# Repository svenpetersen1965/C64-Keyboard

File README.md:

# Status
Realeased: 2026-10-11  
# C64-Keyboard
A mechanical keyboard for the C64.
*	<b>Reset</b>: The keyboard can generate RESET and EXROM RESET signals.
*	<b>Kernal switching</b>: The keyboard can switch between multiple Kernals on an EPROM Kernal adapter.
*	<b>OLED display</b>: An I²C OLED display can be connected to the keyboard.
*	<b>Piezo buzzer</b>: The keyboard includes a piezo buzzer for signaling.
*	<b>USB keyboard</b>: The keyboard can be operated as a USB keyboard for VICE and BMC64.
*	<b>RGB lighting</b>: The keyboard can produce a light show using a WS2812B RGB LED strip.
*	<b>Power LED</b>: The C64's power LED can be connected to the keyboard on either the left or right side and can be made to blink.
*	<b>Additional buttons</b>: Two additional buttons beside the shorter space bar provide additional control functions.
*   <b>Ultimate 64 elite II buttons</b>: Control MENU/FREEZE/RESET with the keyboard. No extra buttons need to be installed

After about 21 months of work, the day has finally come: I’m releasing my Commodore C64 keyboard project on GitHub!

I haven’t been working on it full-time, of course, but I’ve still put several person-months of work into it (most of it for documentation). And I’ve certainly spent a few thousand euros along the way (so you don't have to).

<p align="center">The C64 mechanic Keyboard and the USB-Keyboard version for VICE and BMC64</p>

My goal was to build a complete keyboard, including the keycaps, and figure out a way for others with some DIY skills to build one, too, without having to spend anywhere near as much money.

Let me be clear, though: this isn’t meant to be a cheap replacement for an original C64 keyboard. It’s for people who use a C64, an Ultimate 64, or another C64-compatible system and enjoy mechanical keyboards. If you’d like to build your own keyboard and add some extra functionality to your setup, this project might be just what you’re looking for.

The documentation is around 80 pages long, but most of it consists of pictures, and you don't need to read every single page. I'd really appreciate it, though, if you took the time to understand the important parts. Otherwise, I might end up providing support for years to come, and I'd rather spend that time working on new projects!

The bill of materials (BOM) is quite flexible. You don't need all the components; you can populate only the parts required for your intended setup. I've designed the BOM to make this as straightforward as possible.

However, you should decide which features you need before ordering the components. Even if you fully populate the board, none of the unused circuits will interfere with the keyboard's normal operation.

I'd like to draw your attention to the following important sections of the documentation:
*	<b>Hardware description</b>: <a href="https://github.com/svenpetersen1965/C64-Keyboard/blob/main/C64%20Keyboard%20Standard%20Version/Rev.%202/pdf/C64_Keyb_v2.pdf">Versions without hot-swap sockets</a> for the keyboard switches.
*	<b>Hardware description</b>: <a href="https://github.com/svenpetersen1965/C64-Keyboard/blob/main/C64%20Keyboard%20with%20Hot%20Swap%20Sockets/Rev.%202/pdf/C64_Keyb_HSw_v2.pdf">Versions with hot-swap sockets</a> for the keyboard switches.
*	<b>C64 Keyboard Connector PCB</b>: <a href="https://github.com/svenpetersen1965/C64-Keyboard/blob/main/C64%20Keyboard%20connector%20PCB/Rev.%200/pdf/C64KBConPCB_v0.pdf">Module description</a>. The adapter for the ribbon cable (not required for USB keyboards).
* <b>3D printables</b>: <a href="https://github.com/svenpetersen1965/C64-Keyboard/blob/main/3D%20printables/pdf/C64KB_3D_printables_v1.pdf">Module Description</a>. The mounting frame and the USB keyboard case.
*	<b>Cables</b>: <a href="https://github.com/svenpetersen1965/C64-Keyboard/blob/main/Cables/pdf/Which%20cables%20do%20I%20need.pdf">Which Cables Do I Need?</a>
*	<b>Cables</b>: <a href="https://github.com/svenpetersen1965/C64-Keyboard/blob/main/Cables/pdf/Cable_making.pdf">Cable Making</a>
*	<b>A short guide to making your own keycaps</b>: <a href="https://github.com/svenpetersen1965/C64-Keyboard/blob/main/Keycaps/pdf/How_to_keycaps.pdf">How To: Keycaps</a>.
*	<b>Software documentation</b>: <a href="https://github.com/svenpetersen1965/C64-Keyboard/blob/main/Software/pdf/C64KB_SW_v0.00.pdf">How to use, configure and program the firmware</a>.

The cost of building this project depends on your needs. Buying a fiber laser or a UV printer just for this project probably doesn't make much sense. A dye-sublimation printer is considerably cheaper, but even that isn't essential if you can get hold of pre-printed dye-sublimation transfer paper. The keycaps you can make with this method can look really impressive!

<p align="center">C64 Keyboard with Dye Sub Keycaps</p>

The hot plate required for dye sublimation costs around €27 (as of October 2026). You may already have most of the other tools you need.

<p align="center">Work bench for Dye Sub Keycaps</p>

I've also covered several other ways to add legends to the keycaps, including fiber laser engraving, UV decals and direct UV printing, as well as using original C64 keycaps or Blingboard64 keycaps.

Programming the microcontroller (a Pro Micro) requires nothing more than a USB cable and the free Arduino IDE.

You can easily customize the firmware to suit your needs by enabling or disabling compiler options before uploading it. Simply uncomment or comment out the relevant lines using //.

The only real downside of this project is that you need to solder SMD components (0805, SOT-23, SO-8, SO-14 and SO-16, with a 1.27 mm pin pitch). However, using the hot plate I mentioned earlier for making dye-sublimation keycaps actually makes this quite enjoyable. You can find tutorials on hot-plate soldering on YouTube.

<b>Note</b>: You might like the <a href="https://github.com/svenpetersen1965/C64-Keycap-Handling-Tray/">C64 Keycap Handling Tray</a>, which is a by-product of this project. It is a 3D printable tray, which allows you to keep the oversight of a complete set of C64 keycaps (original and DIY).

# Calculation (as of Oct. 19th, 2025)
The BOM value of the standard keyboard is 98.61€ and 106.99€ of the hot swap keyboard. This does not include shipping and tariffs. Also, the printing of the keycap legends is not included. There are both modules (pro micro and PCF8575) included. The optional LED strip and OLED display are not part of the calculation. 

The price for the switches can vary a lot. I have used the value for Cherry Hyperglide black switches (0.40€) I have already tried switches for 0.23€ each (Gateron g pro milk yellow), which also worked. It really depends on your taste.

The price for the 1U keycaps also vary a lot. I have calculated price of 0.24€, which is the normal price. I have already bought some for 0.13€, too. 

The stabilizers are not cheap components, either. I have assumed 7.79€ for the 7U stabilizer and 6,69€ for the 2U one. I have also used  sets of 1x7U and 4x2U screw mounted stabilizers for 10.99€. Probably, you get that for even less (7€?).

The BOM value of the Connector PCB plus ribbon cable is 3.60€, which is already included in the above calculations for the keyboard.

# Printed keycap sets by Yuzu

With the help by Patrick Horner, I could get some predefined keycap sets from Yuzu:

<b>All White</b><br>
https://yuzukeycaps.com/c/16492bd8-0034-4fa0-9f88-b2e883e93d85

<b>All Black</b><br>
https://yuzukeycaps.com/c/e0255b8e-abf9-4e7c-8b1b-a88284a3ea94

<b>Brown/Orange</b><br>
https://yuzukeycaps.com/c/d665ed74-f621-4a3c-bca7-08b1a41fafc0

<b>Purple Haze 2</b><br>
https://yuzukeycaps.com/c/19eb1e2b-86ea-4545-a4c7-7d6084841e11

<b>White/Blue</b><br>
https://yuzukeycaps.com/c/15ede4f3-3a02-45ec-8442-b245ddb9eab5

<b>White/Grey</b><br>
https://yuzukeycaps.com/c/128e829f-b237-4e82-8b0e-f7e783138823

<b>Note</b><br>
I do not get any funds from Yuzu for linking their page and mentioning their keycaps.<br> 
31.10.2026:<br>
The club PETSCII (X-Keycap) was previously not perfect due to the interpretation of my SVG file for the X legend. I have noticed it from my own order and have corrected it. The keycap sets were corrected and the new URL is provided. The problem was barely visible.

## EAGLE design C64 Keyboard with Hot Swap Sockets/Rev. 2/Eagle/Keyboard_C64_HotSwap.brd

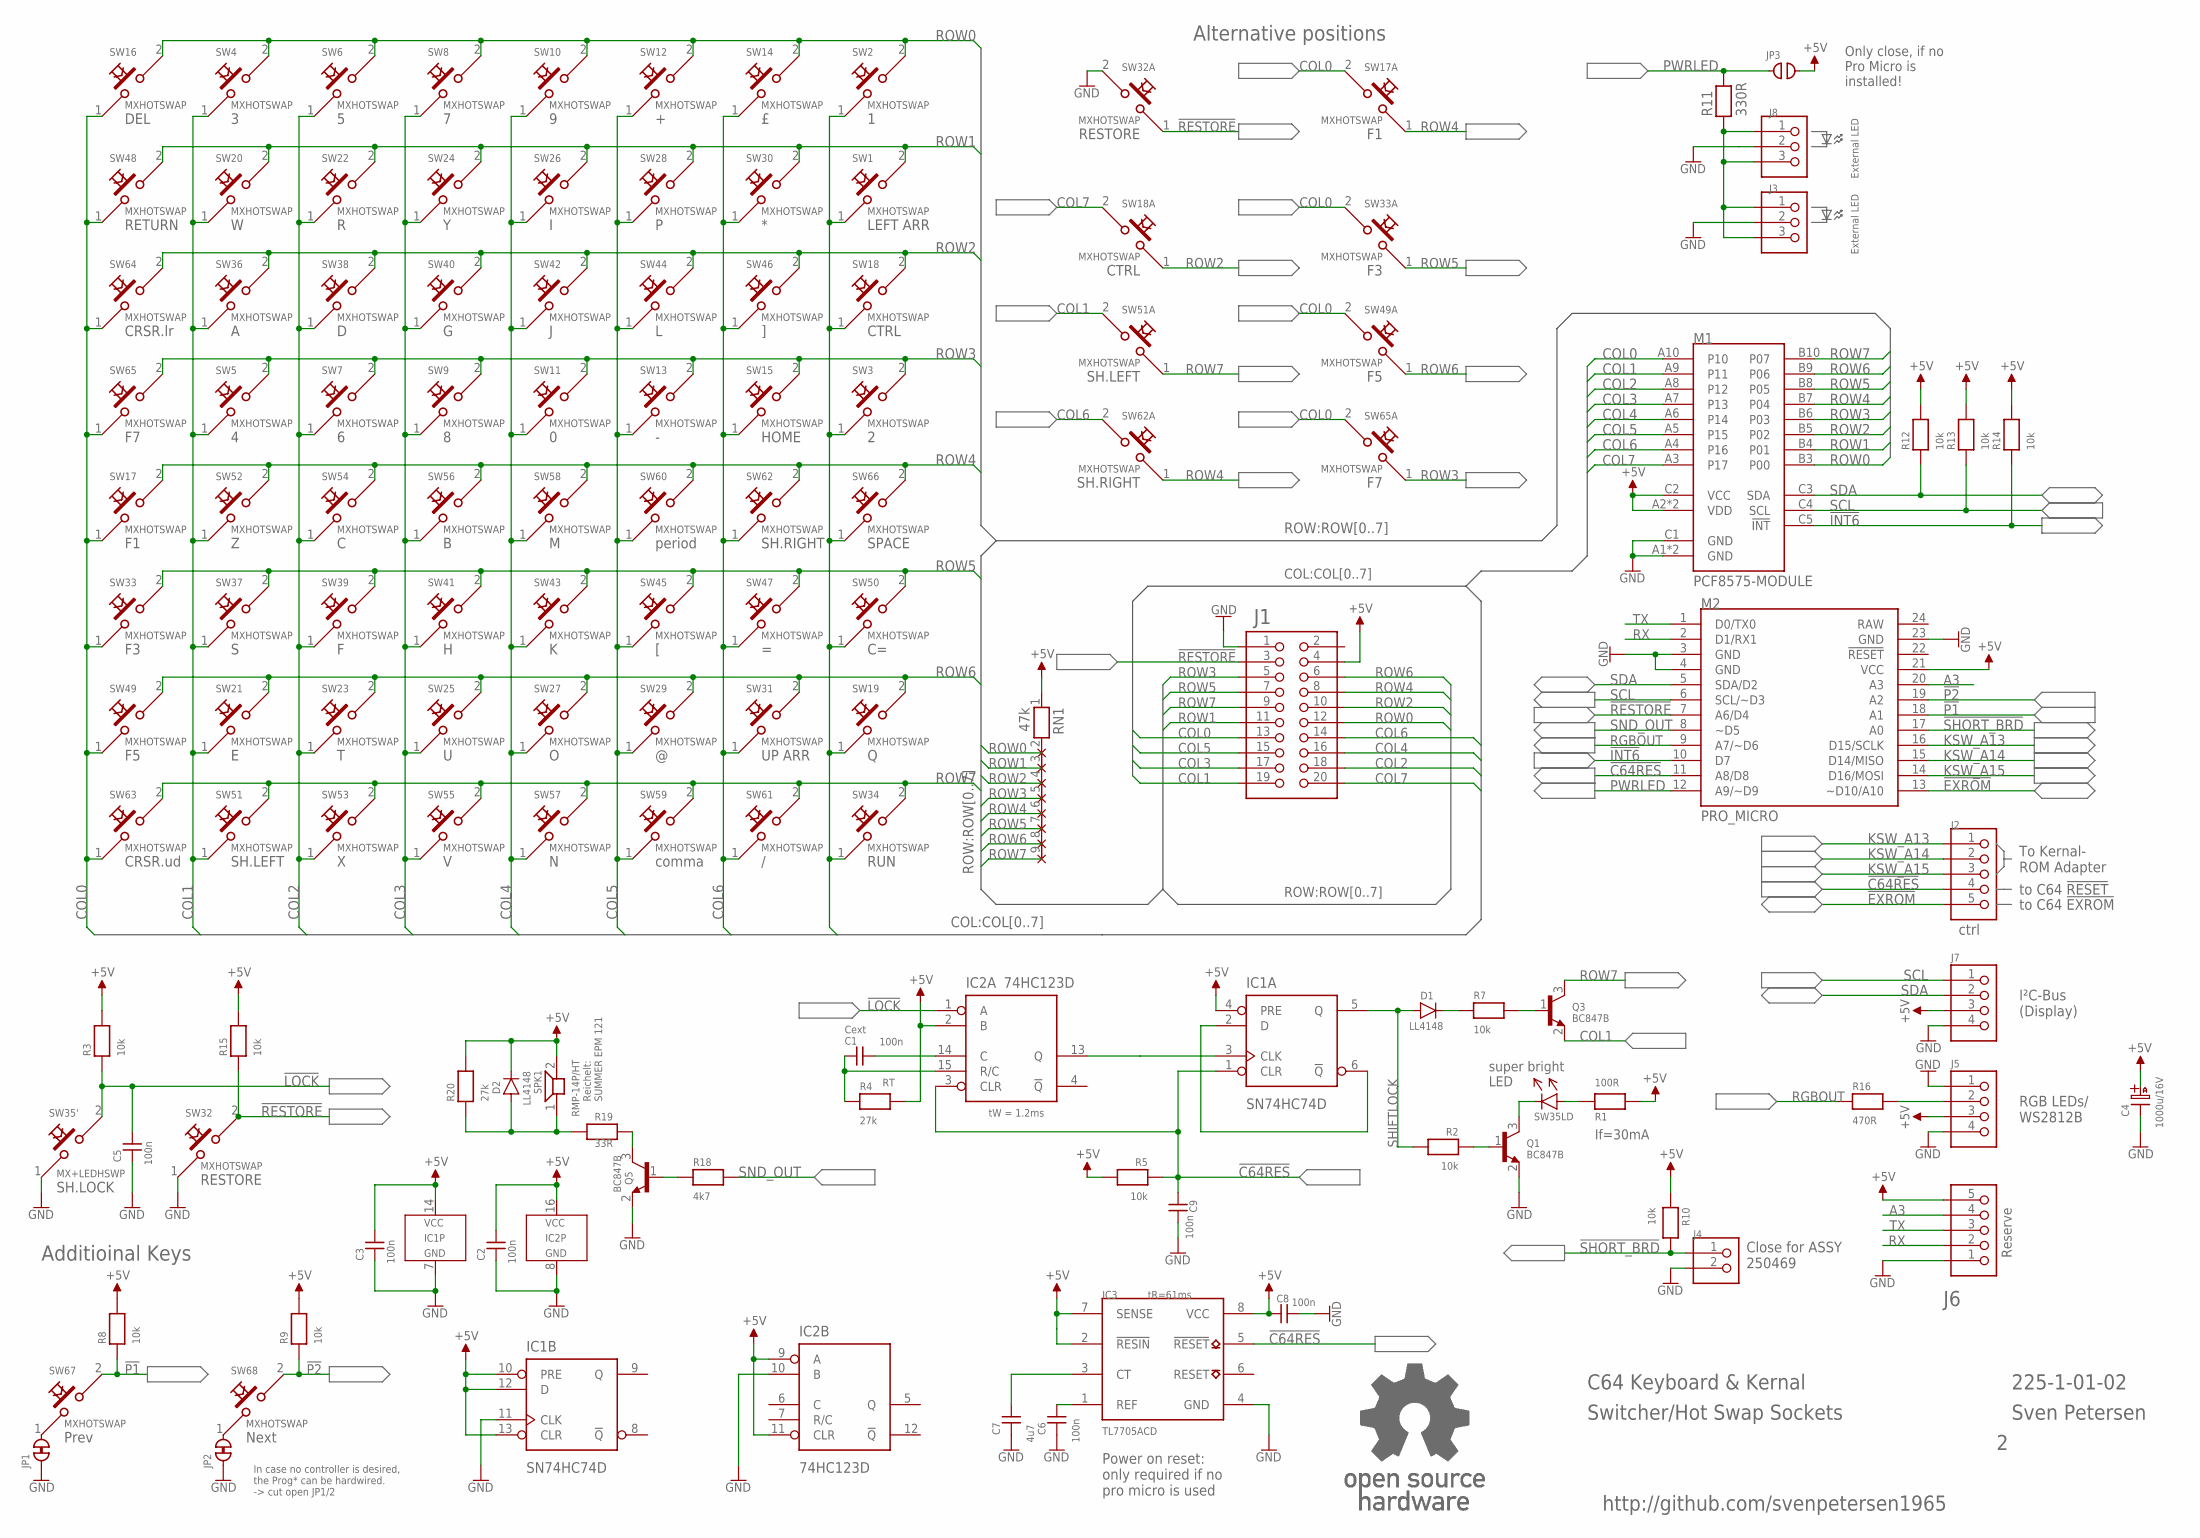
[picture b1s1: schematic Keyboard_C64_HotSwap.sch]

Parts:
C1, C2, C3, C5, C6, C8, C9: 100n; 0805
C4: 1000u/16V; C30X16L
C7: 4u7; 0805
D1, D2: LL4148; SOD80C
IC1: SN74HC74D; SO-14
IC2: 74HC123D; SO-16
IC3: TL7705ACD; SO8
J1: PINHD-2X10WH; 2X10WH
J2, J6: PINHD-1X590°; 1X05/90
J3, J8: PINHD-1X3/90; 1X03/90
J4: PINHD-1X2/90; 1X02/90
J5, J7: PINHD-1X4/90; 1X04/90
JP1, JP2: CLOSED; CP_CL
JP3: OPEN; CP_OP
M1: PCF8575-MODULE; PCF8575MODUL
M2: PRO_MICRO
Q1, Q3, Q5: BC847B; SOT23
R1: 100R; 0805
R2, R3, R5, R7, R8, R9, R10, R12, R13, R14, R15: 10k; 0805
R4, R20: 27k; 0805
R11: 330R; 0805
R16: 470R; 0805
R18: 4k7; 0805
R19: 33R; 0805
RN1: 47k; RN-9
SPK1: RMP-14P/HT
SW1, SW2, SW3, SW4, SW5, SW6, SW7, SW8, SW9, SW10, SW11, SW12, SW13, SW14, SW15, SW16, SW17, SW17A, SW18, SW18A, SW19, SW20, SW21, SW22, SW23, SW24, SW25, SW26, SW27, SW28, SW29, SW30, SW31, SW32, SW32A, SW33, SW33A, SW34, SW36, SW37, SW38, SW39, SW40, SW41, SW42, SW43, SW44, SW45, SW46, SW47, SW48, SW49, SW49A, SW50, SW51, SW51A, SW52, SW53, SW54, SW55, SW56, SW57, SW58, SW59, SW60, SW61, SW62, SW62A, SW63, SW64, SW65, SW65A, SW66, SW67, SW68: MXHOTSWAP; CHERRYMX_HOTSWAP
SW35: MX+LEDHSWP; CHERRYMX_HSWP_LD
U$90: OPEN_SOURCE_HW; OPENHW

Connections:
!C64RES: C9.1, IC1.1 (CLR), IC2.3 (CLR), IC3.5 (!RESET), J2.4, M2.11 (A8/D8), R5.1
!EXROM: J2.5, M2.13 (~D10/A10)
!INT6: M1.C5 (!INT), M2.10 (D7), R14.1
!LOCK: C5.2, IC2.1 (A), R3.1, SW35.2
!P1: M2.18 (A1), R8.1, SW67.2
!P2: M2.19 (A2), R9.1, SW68.2
!RESTORE: J1.3, M2.7 (A6/D4), R15.1, SW32.2, SW32A.1
!SHORT_BRD: J4.1, M2.17 (A0), R10.2
+5V: C2.2, C3.2, C4.A (+), D2.K, IC1.4 (PRE), IC1.10 (PRE), IC1.12 (D), IC1.13 (CLR), IC1.14 (VCC), IC2.2 (B), IC2.9 (A), IC2.11 (CLR), IC2.16 (VCC), IC3.2 (!RESIN), IC3.7 (SENSE), J1.4, J5.3, J6.5, J7.3, JP3.2, M1.A2 (VDD), M1.B2 (VDD), M1.C2 (VCC), M2.21 (VCC), R1.2, R3.2, R4.2, R5.2, R8.2, R9.2, R10.1, R12.2, R13.2, R14.2, R15.2, R20.2, RN1.1, SPK1.2
A3: J6.4, M2.20 (A3)
COL0: J1.13, M1.A10 (P10), SW16.1, SW17.1, SW17A.2, SW33.1, SW33A.2, SW48.1, SW49.1, SW49A.2, SW63.1, SW64.1, SW65.1, SW65A.2
COL1: J1.19, M1.A9 (P11), Q3.2 (E), SW4.1, SW5.1, SW20.1, SW21.1, SW36.1, SW37.1, SW51.1, SW51A.2, SW52.1
COL2: J1.18, M1.A8 (P12), SW6.1, SW7.1, SW22.1, SW23.1, SW38.1, SW39.1, SW53.1, SW54.1
COL3: J1.17, M1.A7 (P13), SW8.1, SW9.1, SW24.1, SW25.1, SW40.1, SW41.1, SW55.1, SW56.1
COL4: J1.16, M1.A6 (P14), SW10.1, SW11.1, SW26.1, SW27.1, SW42.1, SW43.1, SW57.1, SW58.1
COL5: J1.15, M1.A5 (P15), SW12.1, SW13.1, SW28.1, SW29.1, SW44.1, SW45.1, SW59.1, SW60.1
COL6: J1.14, M1.A4 (P16), SW14.1, SW15.1, SW30.1, SW31.1, SW46.1, SW47.1, SW61.1, SW62.1, SW62A.2
COL7: J1.20, M1.A3 (P17), SW1.1, SW2.1, SW3.1, SW18.1, SW18A.2, SW19.1, SW34.1, SW50.1, SW66.1
GND: C2.1, C3.1, C4.K (-), C5.1, C6.1, C7.1, C8.2, C9.2, IC1.7 (GND), IC1.11 (CLK), IC2.8 (GND), IC2.10 (B), IC3.4 (GND), J1.1, J3.2, J4.2, J5.1, J5.4, J6.1, J7.4, J8.2, JP1.1, JP2.1, M1.A1 (GND), M1.B1 (GND), M1.C1 (GND), M2.3 (GND), M2.4 (GND), M2.23 (GND), Q1.2 (E), Q5.2 (E), SW32.1, SW32A.2, SW35.1
KSW_A13: J2.1, M2.16 (D15/SCLK)
KSW_A14: J2.2, M2.15 (D14/MISO)
KSW_A15: J2.3, M2.14 (D16/MOSI)
LOCK: IC1.3 (CLK), IC2.13 (Q)
unnamed: R1.1, SW35.LDA (A)
unnamed: Q1.3 (C), SW35.LDC (K)
unnamed: Q1.1 (B), R2.1
unnamed: C1.2, IC2.14 (C)
unnamed: IC1.2 (D), IC1.6 (!Q)
unnamed: D1.K, R7.1
unnamed: Q3.1 (B), R7.2
unnamed: Q5.1 (B), R18.1
unnamed: J3.1, J3.3, J8.1, J8.3, R11.1
unnamed: Q5.3 (C), R19.2
unnamed: D2.A, R19.1, R20.1, SPK1.1
unnamed: J5.2, R16.2
unnamed: JP1.2, SW67.1
unnamed: JP2.2, SW68.1
unnamed: C1.1, IC2.15 (R/C), R4.1
unnamed: C8.1, IC3.8 (VCC)
unnamed: C6.2, IC3.1 (REF)
unnamed: C7.2, IC3.3 (CT)
PWRLED: JP3.1, M2.12 (A9/~D9), R11.2
RAW: M2.24 (RAW)
RGBOUT: M2.9 (A7/~D6), R16.1
ROW0: J1.12, M1.B3 (P00), RN1.2, SW2.2, SW4.2, SW6.2, SW8.2, SW10.2, SW12.2, SW14.2, SW16.2
ROW1: J1.11, M1.B4 (P01), RN1.3, SW1.2, SW20.2, SW22.2, SW24.2, SW26.2, SW28.2, SW30.2, SW48.2
ROW2: J1.10, M1.B5 (P02), RN1.4, SW18.2, SW18A.1, SW36.2, SW38.2, SW40.2, SW42.2, SW44.2, SW46.2, SW64.2
ROW3: J1.5, M1.B6 (P03), RN1.5, SW3.2, SW5.2, SW7.2, SW9.2, SW11.2, SW13.2, SW15.2, SW65.2, SW65A.1
ROW4: J1.8, M1.B7 (P04), RN1.6, SW17.2, SW17A.1, SW52.2, SW54.2, SW56.2, SW58.2, SW60.2, SW62.2, SW62A.1, SW66.2
ROW5: J1.7, M1.B8 (P05), RN1.7, SW33.2, SW33A.1, SW37.2, SW39.2, SW41.2, SW43.2, SW45.2, SW47.2, SW50.2
ROW6: J1.6, M1.B9 (P06), RN1.8, SW19.2, SW21.2, SW23.2, SW25.2, SW27.2, SW29.2, SW31.2, SW49.2, SW49A.1
ROW7: J1.9, M1.B10 (P07), Q3.3 (C), RN1.9, SW34.2, SW51.2, SW51A.1, SW53.2, SW55.2, SW57.2, SW59.2, SW61.2, SW63.2
RX: J6.2, M2.2 (D1/RX1)
SCL: J7.1, M1.C4 (SCL), M2.6 (SCL/~D3), R13.1
SDA: J7.2, M1.C3 (SDA), M2.5 (SDA/D2), R12.1
SHIFTLOCK: D1.A, IC1.5 (Q), R2.2
SND_OUT: M2.8 (~D5), R18.2
TX: J6.3, M2.1 (D0/TX0)

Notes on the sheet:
Alternative positions
Additioinal Keys
To Kernal- ROM Adapter
to C64 !RESET
Close for ASSY 250469
to C64 !EXROM
ctrl
I²C-Bus (Display)
External LED
Reichelt: SUMMER EPM 121
225-1-01-02
Sven Petersen
C64 Keyboard & Kernal
Switcher/Hot Swap Sockets
http://github.com/svenpetersen1965
RGB LEDs/ WS2812B
In case no controller is desired, the Prog* can be hardwired. -> cut open JP1/2
Reserve
Only close, if no Pro Micro is installed!
super bright LED
If=30mA
Cext
tW = 1.2ms
Power on reset: only required if no pro micro is used
tR=61ms

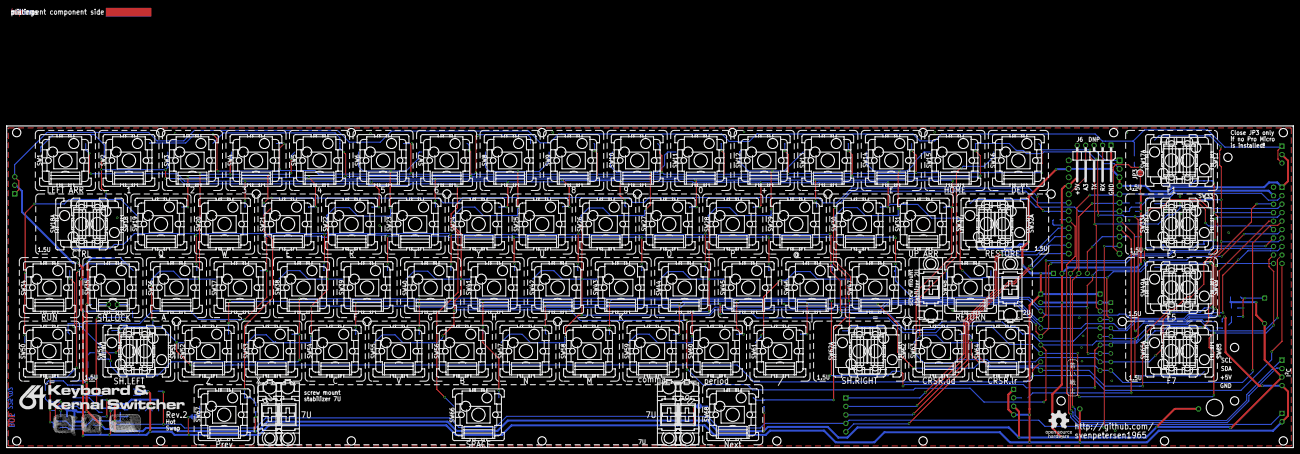
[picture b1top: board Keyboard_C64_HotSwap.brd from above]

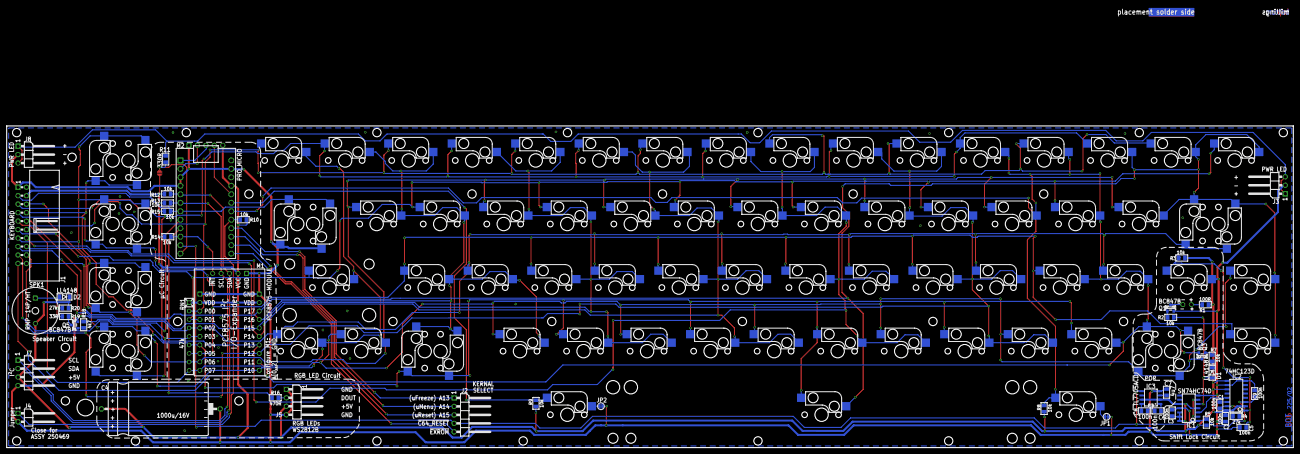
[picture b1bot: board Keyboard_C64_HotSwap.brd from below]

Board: 2 copper layers, 385.6 x 96.4 mm, 206 parts (48 on the bottom side), 57 nets.

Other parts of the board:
U$92, U$93, U$94, U$95, U$96, U$97, U$98, U$106: KCAP_1_5U
U$99, U$100, U$101, U$102, U$103, U$107, U$108, U$109, U$110, U$111, U$112, U$113, U$114, U$115, U$116, U$117, U$118, U$119, U$120, U$121, U$122, U$123, U$124, U$125, U$126, U$127, U$128, U$129, U$130, U$131, U$132, U$133, U$134, U$135, U$136, U$137, U$138, U$139, U$140, U$141, U$142, U$143, U$144, U$145, U$146, U$147, U$148, U$149, U$150, U$151, U$152, U$153, U$154, U$155, U$156, U$157, U$158, U$159: KCAP_1U
U$104: KCAP_7U
U$105: KCAP_2U
U$161: 2LAYER
U$162: PCB-TITLE/
U$164: C64_KEYS
U$172, U$175, U$181: STABIL_PIN_SCREW_L
U$173, U$174, U$180: STABIL_PIN_SCREW
U$176: 64KB
U$178: SVEN_TAG

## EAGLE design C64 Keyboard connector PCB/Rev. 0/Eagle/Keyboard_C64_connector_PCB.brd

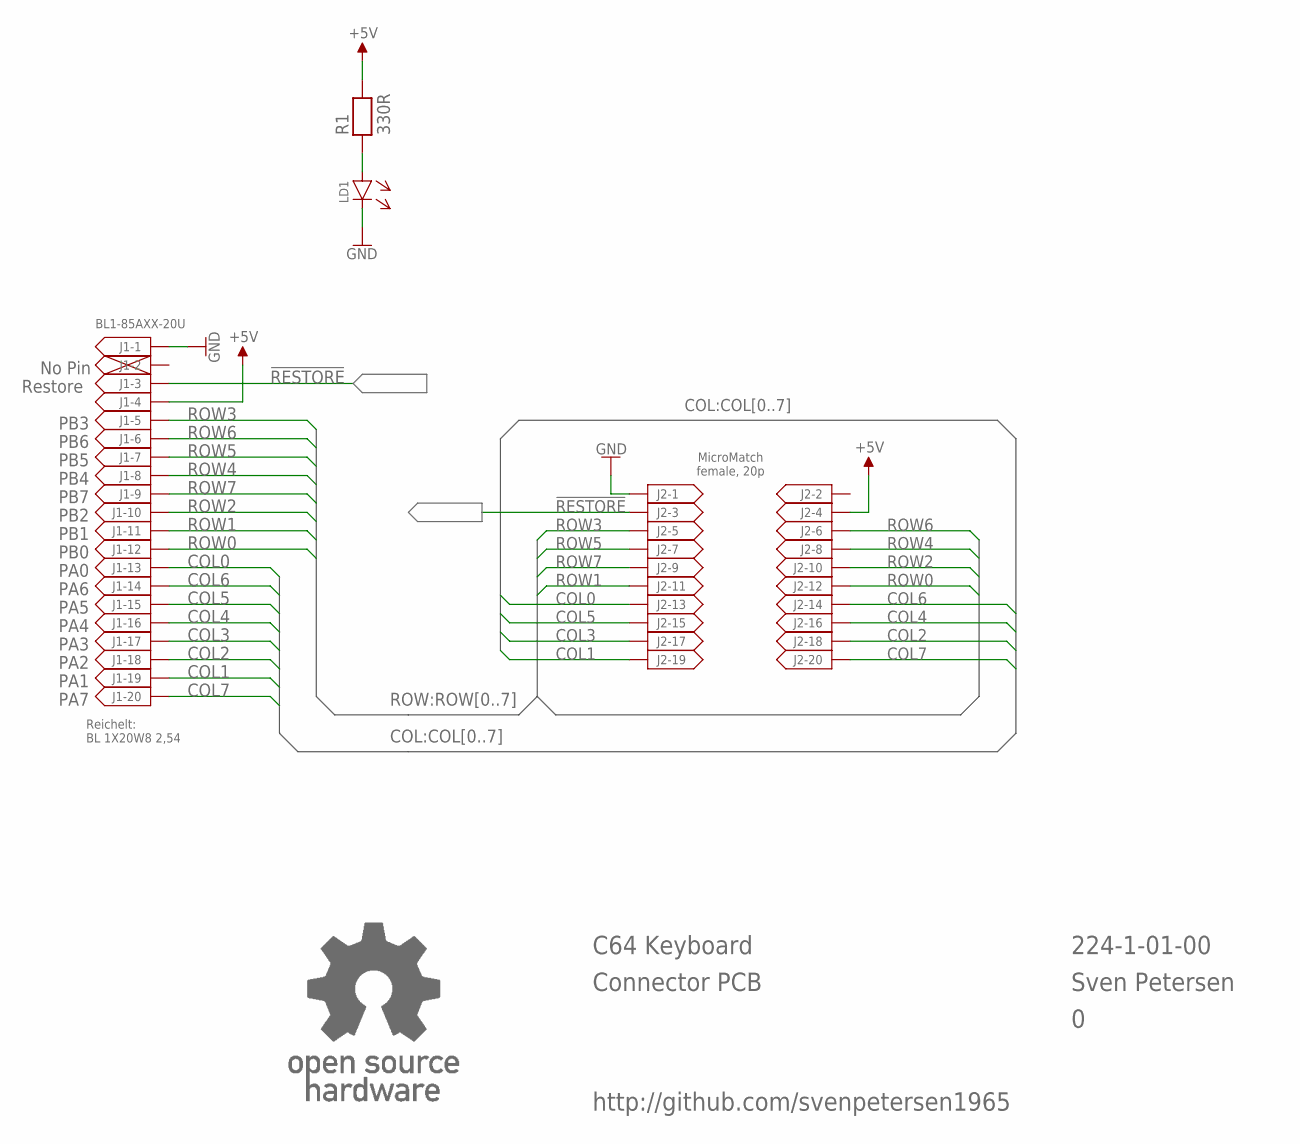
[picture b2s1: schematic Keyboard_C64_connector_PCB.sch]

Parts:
J1: BL1-85AXX-20U
J2: MICMA20B
LD1: 3MM
R1: 330R; R-10
U$9: OPEN_SOURCE_HW; OPENHW

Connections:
!RESTORE: J1.3, J2.3
+5V: J1.4, J2.4, R1.2
COL0: J1.13, J2.13
COL1: J1.19, J2.19
COL2: J1.18, J2.18
COL3: J1.17, J2.17
COL4: J1.16, J2.16
COL5: J1.15, J2.15
COL6: J1.14, J2.14
COL7: J1.20, J2.20
GND: J1.1, J2.1, LD1.C (K)
unnamed: LD1.A, R1.1
ROW0: J1.12, J2.12
ROW1: J1.11, J2.11
ROW2: J1.10, J2.10
ROW3: J1.5, J2.5
ROW4: J1.8, J2.8
ROW5: J1.7, J2.7
ROW6: J1.6, J2.6
ROW7: J1.9, J2.9

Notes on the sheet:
PB3
PB6
PB5
PB4
PB7
PB2
PB1
PB0
PA0
PA6
PA5
PA4
PA3
PA2
PA1
PA7
No Pin
Restore
C64 Keyboard
Connector PCB
224-1-01-00
Sven Petersen
Reichelt: BL 1X20W8 2,54
http://github.com/svenpetersen1965
MicroMatch female, 20p

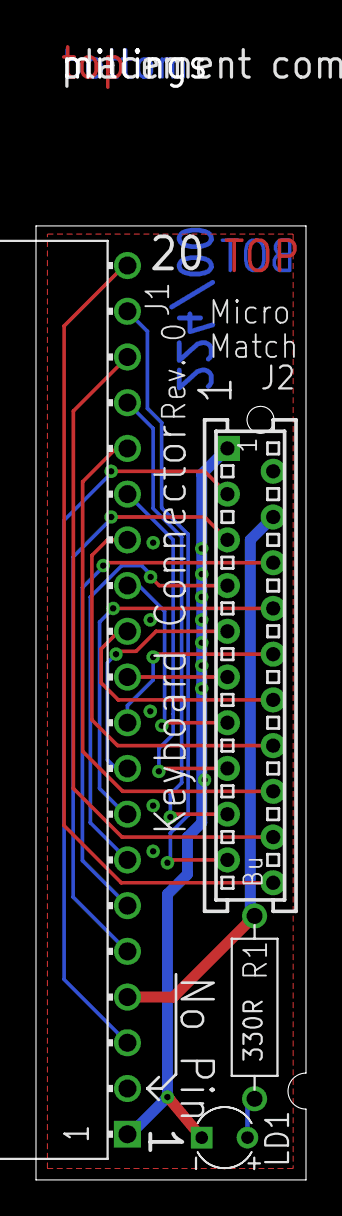
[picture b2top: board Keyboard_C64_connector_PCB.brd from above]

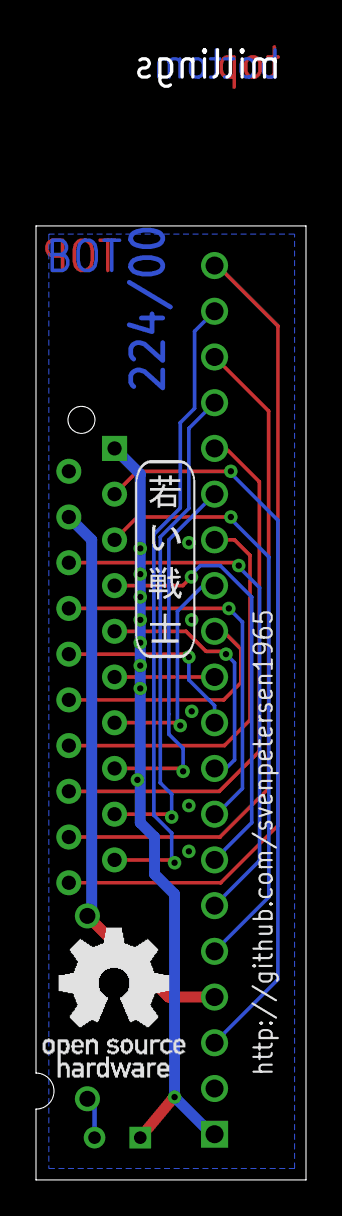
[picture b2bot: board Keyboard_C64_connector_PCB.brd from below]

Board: 2 copper layers, 15.0 x 53.0 mm, 8 parts (2 on the bottom side), 20 nets.

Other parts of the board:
U$6: 2LAYER
U$7: PCB-TITLE/
U$8: SVEN_TAG

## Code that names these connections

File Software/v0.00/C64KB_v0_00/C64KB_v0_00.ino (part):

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#define buzzer   5
#define rgbPin   6
#define nC64res  8
#define pwrLed   9
#define nExrom   10
#ifndef Ultimate
  #define kswA13   15
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/* constants */
const bool recover_empty = true;     //enable recover to Kernal one, in case an empty/not working kernal was selected
const int  NumKernal = 8;            //This is the highest valid Kernal number
const int resetCount = 1500;         // count 1.5 seconds of RESTORE Key before Reset is performed
const int EXROMCount = 3000;         // count 3.0 seconds of RESTORE Key before Reset is performed
const int restoreFix = 100;          // count 300ms of RESTORE Key before restore fix is performed 
const int Sig_time = 500;            // constant for signalling duration

// states for restoreSemaphore 
#define rIdle  0                     // the RGB routine is executed, keyboard scan, display refresh 
#define rFix   1                     // calling the RESTORE fix function
#define rReset 2                     // performing a C64 reset
#define rExrom 3                     // performing a C64 EXROM reset
#define kPrev  4                     // the "previous" key + RESTORE was detected
#define kNext  5                     // the "next" key  + RESTORE was detected
#define mNext  6                     // the "previous" key was detected
#define mPrev  7                     // the "next" key was detected
#define sig1   8                     // signal (Power LED and buzzer): Ready for RESET
#define sig2   9                     // signal (Power LED and buzzer): Ready for EXROM RESET

// timing 
#define Debounce   50                 // Debounce Time in ms
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byte KOffset = 0;                        // offset for kernal number
byte KNumber = 0;                        // Kernal number
byte KAddr = 0;                          // Address bits for Kernal
int  countup = 0;                        // counter for restore key time measurement
int  KMax;                               // holds the highest Kernal Number
byte modeNumber;                         // number of the RGB mode executes 
bool USBkbActive = false;                // true, when USB keyboard is activated
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volatile int t1_ticks = 0;               // counts the timer1 interrupts 
volatile int msCntDwn = 0;               // milli seconds countdown (counts to zero)

bool exromMode = 0;                      // exrom mode for reset
int kaddr = 0;                           // kernam address bits (A13..15)

// returns the value of the timer 1ms countdown 
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  pinMode( nC64res, OUTPUT);                          // issue a reset pulse for the C64
  waitMs( 100 );                                      // 100ms delay
  if (exromMode == 1) {
    pinMode( nExrom, OUTPUT );                        // output low on /EXROM
  }
  waitMs( 300 );                                      // pulse duration: 100+300ms
  pinMode( nC64res, INPUT );                          // deactivate reset line
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  digitalWrite( pwrLed, 1 );                          // turn power LED on again.
}

// issues a pulse trail on the RESTORE pin "RESTORTE Fix"
void restorePulses (void) {
  int i;

  digitalWrite( nRestore, 0 );                        // prepare the RESTORE pin for the pulse trail
  for (i=0; i<numPulses; i++ ) {
    pinMode( nRestore, OUTPUT );                      // switching pin mode bwtween OUTPUT and INPUT mimicks an open collector transistor output
    tone( buzzer, 6000 );
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      // Bit7 col   1              <-               CTRL       2          SPACE            C=             Q               STOP
                  { KEY_1,         KEY_TILDE,       KEY_TAB,   KEY_2,     KEY_SPACE,       KEY_LEFT_CTRL, KEY_Q,          KEY_ESC }
    };
    #define KEY_RESTORE   KEY_PAGE_UP   // define RESTORE key
  #endif

  // German positional keyboard layout
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      // Bit7 col   1              <-               CTRL       2          SPACE            C=             Q               STOP
                  { KEY_1,         KEY_TILDE,       KEY_TAB,   KEY_2,     KEY_SPACE,       KEY_LEFT_CTRL, KEY_Q,          KEY_ESC }
    };
    #define KEY_RESTORE   KEY_F12 // define restore key
  #endif
  
  // Swedish positional keyboard layout
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
// timer (the heartbeat of the complete software)
ISR(TIMER1_COMPA_vect) {                         // function which will be called when an interrupt occurs at timer 1 every 1ms
  static bool restoreKey = 0;                    // status of the restore key
  static bool oldRestoreKey = 0;                 // previous status of the restore key
  static int  restoreDebounce = 0;               // count down for debouncing the restore key
  static bool restoreState = 0;                  // debounced state of the RESTORE key
  static int  restoreCount = 0;                  // counter for measuring, how long the restore key is pushed down
  static bool prevKey = 0;                       // status of the "Previous" key
  static bool oldPrevKey = 0;                    // previous status of the "Previous" key
  static int  prevDebounce = 0;                  // count down for debouncing the "Previous" key
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      if (prevKey == true) {             // prev key valid?
        if (restoreState == true) {      // is restore key pressed?
          restoreSemaphore = kPrev;      // signalize "previous kernal"
          restoreCount = 0;              // reset restore count
        }
        else {                           // no restore pressed:
          restoreSemaphore = mPrev;      // signalize "previous mode"
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      if (nextKey == true) {             // prev key valid?
        if (restoreState == true) {      // is restore key pressed?
          restoreSemaphore = kNext;      // signalize "next kernal"
          restoreCount = 0;              // reset restore count
        }
        else {                           // no restore pressed:
          restoreSemaphore = mNext;      // signalize "next mode"
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  digitalWrite( kswA15, LOW );        // kernal ROM upper address bit A15
#endif

  pinMode( nRestore, INPUT );         // RESTORE key input (switches to output for the RESTORE fix pulses)
  pinMode( buzzer, OUTPUT );          // output for the piezo buzzer
  pinMode( rgbPin, OUTPUT );          // output pin  for the WS2812B RGB LED strip
  pinMode( nC64res, INPUT );          // acting like open collector
  pinMode( shortBrd, INPUT );         // shortboard jumper    
  pinMode( pwrLed,OUTPUT );           // power LED output
  pinMode( nExrom, INPUT );           // EXROM: acts like an open collector output. Can pull low as output
  #ifndef Ultimate                    
    pinMode( kswA13, OUTPUT );        // kswA13...15 are all low and the pin mode is output 
    pinMode( kswA14, OUTPUT );        
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    EEPROM.write(eeRGB, modeNumber);                      // and written back to EEPROM (non volatile)
  }

  exromMode = 0;                               // initialize exrom mode (for reset). 0 = no exrom reset

  #ifndef Ultimate  
    /* Control outputs (for Kernal Adaptor and C64) */
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      #endif 
      #ifndef USBkeyboard                      // if it is a real C64 connected
        #ifndef Ultimate                       // and not an ultimate (the ultimate does not require a restore puls train)
          restorePulses();                     // issue a pulse trail on the RESTORE pin.
        #endif
      #endif  
      restoreSemaphore = rIdle;                // reset the restore semaphore to idle
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      #ifdef Ultimate                          // in Ultimate 64 mode => Button uRESET
        digitalWrite(uReset, LOW);
        digitalWrite( pwrLed, 0 );             // Signaling active: turn Power LED off
        pinMode( nC64res, OUTPUT);             // resetting the shift lock status
        pinMode(uReset, OUTPUT);               // "press" button uReset 
        waitMs(uTime);                         // wait some time
        pinMode(uReset, INPUT);                // release the button: Switch to Hi-Z
        pinMode( nC64res, INPUT );             // release the reset for the shift lock state flipflop
        digitalWrite( pwrLed, 1 );             // power LED on again
      #else
        resetC64( false );                     // C64: reset C64 in normal mode
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      #ifdef Ultimate                          // in Ultimate 64 mode => Button uRESET
        digitalWrite(uReset, LOW);
        digitalWrite( pwrLed, 0 );             // Signaling active: turn Power LED off
        pinMode( nC64res, OUTPUT);             // resetting the shift lock status
        pinMode(uReset, OUTPUT);               // "press" button uReset 
        waitMs(uTime);                         // wait some time
        pinMode(uReset, INPUT);                // release the button: Switch to Hi-Z
        pinMode( nC64res, INPUT );             // release the reset for the shift lock state flipflop
        digitalWrite( pwrLed, 1 );             // power LED on again
      #endif
      setRefreshCntDwn(2000);                  // Set display refresh countdown to 2 secs.
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
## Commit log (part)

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2026-06-04 3D printed frame
2026-06-04 Print trays
    Trays for keycap fabrication
2026-06-04 Scans of C64C key caps
2026-06-04 The legends of the keycaps
2026-06-04 Exports in PNG format
